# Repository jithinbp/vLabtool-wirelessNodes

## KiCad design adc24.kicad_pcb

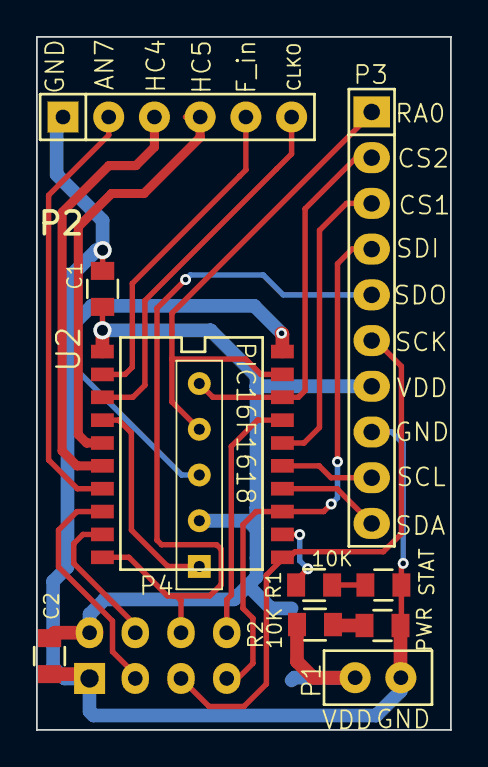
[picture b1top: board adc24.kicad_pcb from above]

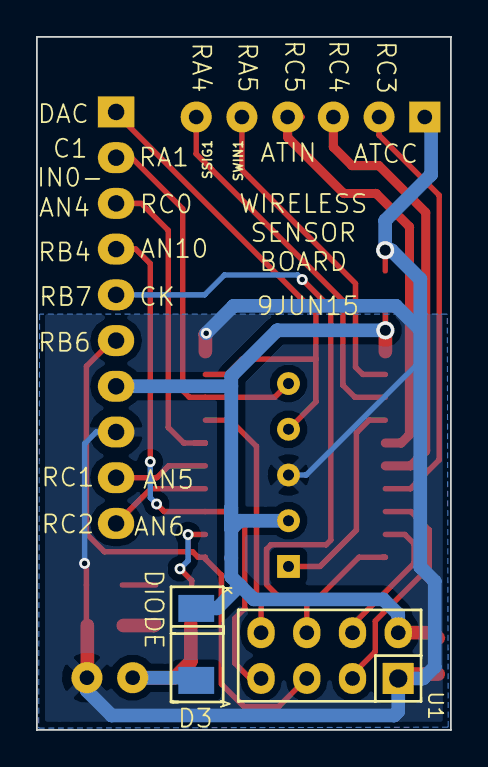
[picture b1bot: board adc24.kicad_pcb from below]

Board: 2 copper layers, 23.0 x 38.5 mm, 13 parts (2 on the bottom side), 23 nets.

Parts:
C1, C2: .1u; C_0805
D3: DIODE; Diode-SMA_Standard
P1: POWER; myPin_Header_Straight_1x02
P2: gpio; myPin_Header_Straight_1x06
P3: I2C/SPI; Pin_Header_Straight_1x10-oval
P4: PROG; PICKIT-PROG
PWR: LED; C_0805
R1, R2: 10K; R_0805
STAT: LED; C_0805
U1: NRF24L01; NRF-8PIN
U2: PIC16F1618; SOIC-20-W

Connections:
/MCLR: P4.1, U2.4
/RA0: P3.1, P4.4, U2.19
/RA1: P3.2, P4.5, U2.18
/RA2: U1.8, U2.17
/RA4: P2.6, U2.3
/RA5: P2.5, U2.2
/RC0: P3.3, U2.16
/RC3: P2.2, U2.7
/RC4: P2.3, U2.6
/RC5: P2.4, U2.5
/SCK: P3.6, U1.5, U2.11
/SCL: P3.9, U2.15
/SDA: P3.10, U2.14
/SDI: P3.4, U1.7, U2.13
/SDO: P3.5, U1.6, U2.10
/VDD: C1.1, C2.2, D3.2, P3.7, P4.2, U1.2, U2.1
GND: C1.2, C2.1, P1.1, P2.1, P3.8, P4.3, PWR.2, STAT.2, U1.1, U2.20
unnamed: R1.2, STAT.1
unnamed: PWR.1, R2.1
unnamed: D3.1, P1.2, R2.2
unnamed: R1.1, U2.12
unnamed: U1.3, U2.8
unnamed: U1.4, U2.9

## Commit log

2015-08-24 add readme
